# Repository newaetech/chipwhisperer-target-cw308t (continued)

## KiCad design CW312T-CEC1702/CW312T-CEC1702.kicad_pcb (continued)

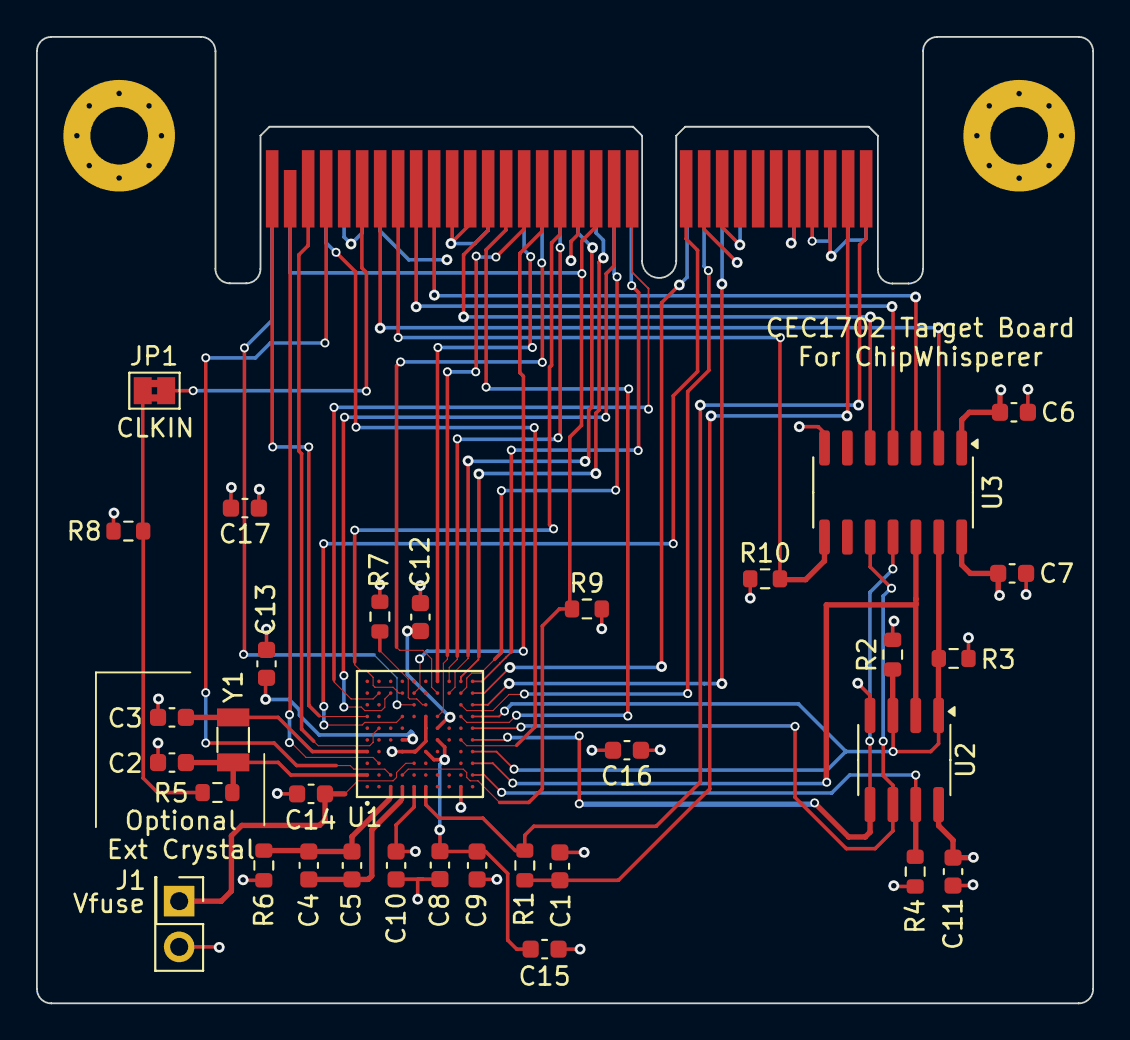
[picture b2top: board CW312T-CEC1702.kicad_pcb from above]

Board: 4 copper layers, 58.7 x 53.7 mm, 38 parts (0 on the bottom side), 47 nets.

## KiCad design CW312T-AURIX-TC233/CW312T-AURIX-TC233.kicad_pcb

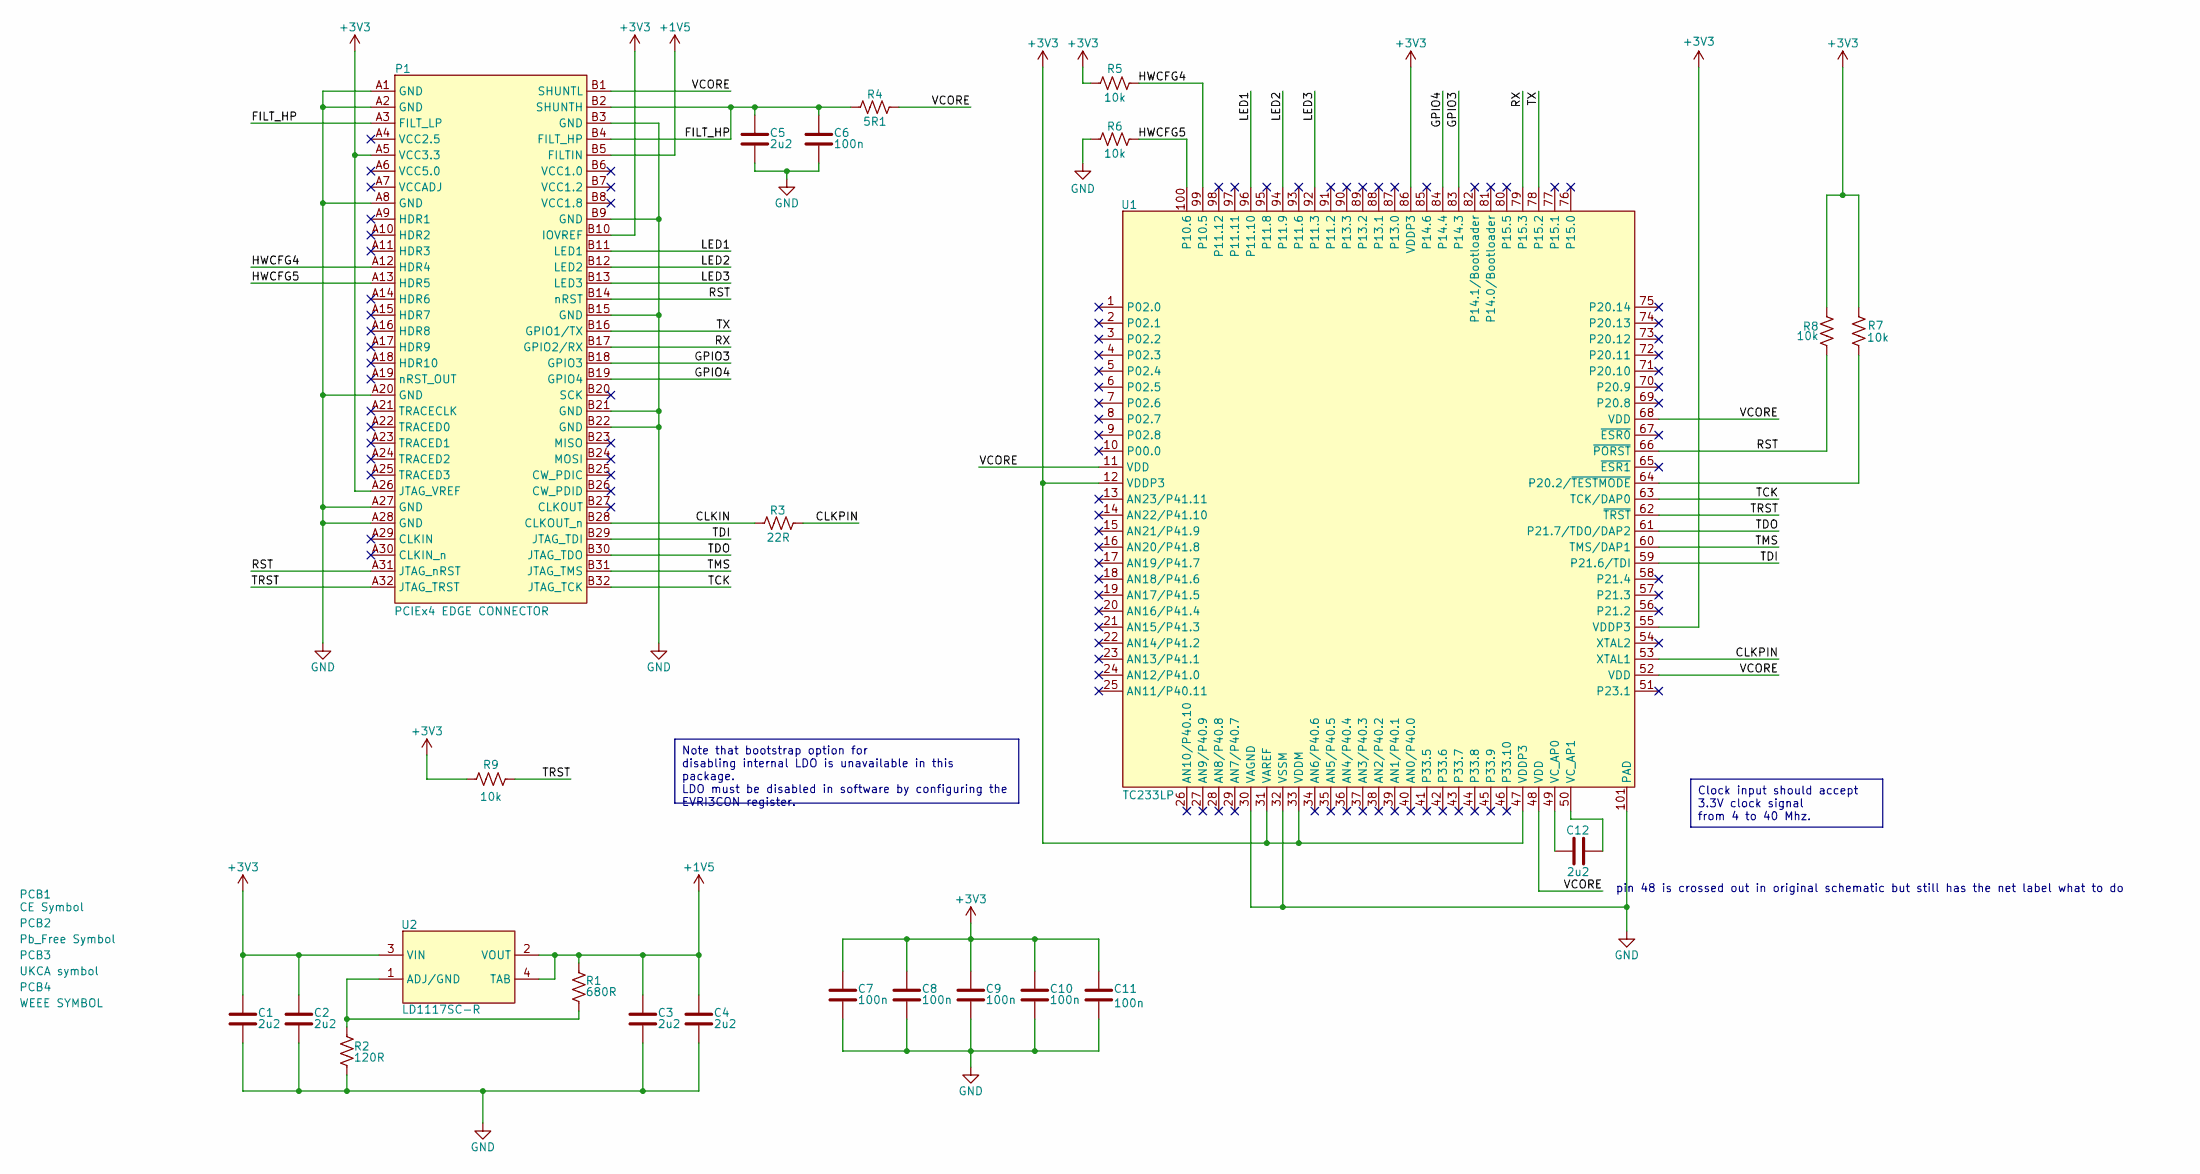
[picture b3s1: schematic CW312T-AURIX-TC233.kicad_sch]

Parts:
C1, C2, C3, C4, C5, C12: CAP_2u2_10V_0603; C_0603_1608Metric; Manufacturer Part Number CC0603KPX7R6BB225
C6, C7, C8, C9, C10, C11: CAP_100n_50V_0603; C_0603_1608Metric; Manufacturer Part Number CC0603KRX7R9BB104
P1: PCIEx4 EDGE CONNECTOR; CW312_Template
PCB1: CE Symbol; CE-Logo_8.5x6mm_SilkScreen
PCB2: Pb_Free Symbol; Pb_Free_8.0x8.0mm_SilkScreen
PCB3: UKCA symbol; UKCA-Logo_8x8mm_SilkScreen
PCB4: WEEE SYMBOL; WEEE-Logo_5.6x8mm_SilkScreen
R1: RES_680R_0603; R_0603_1608Metric; Manufacturer Part Number RC0603FR-07680RL
R2: RES_120R_0603; R_0603_1608Metric; Manufacturer Part Number RC0603FR-07120RL
R3: RES_22R_0603; R_0603_1608Metric; Manufacturer Part Number RC0603FR-0722RL
R4: RES_5R1_0603; R_0603_1608Metric; Manufacturer Part Number RC0603FR-075R1L
R5, R6, R7, R8, R9: RES_10k_0603; R_0603_1608Metric; Manufacturer Part Number RC0603FR-0710KL
U1: TC233LP32F200NACKXUMA1; TQFP-100-1EP_14x14mm_P0.5mm_EP5x5mm; Manufacturer Part Number TC233LP32F200NACKXUMA1
U2: LD1117SC-R; SOT-223; Manufacturer Part Number LD1117SC-R

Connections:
+1V5: C3.2, C4.2, P1.B5 (FILTIN), R1.2, U2.2 (VOUT), U2.4 (TAB)
+3V3: C1.2, C2.2, C7.2, C8.2, C9.2, C10.2, C11.2, P1.A5 (VCC3.3), P1.A26 (JTAG_VREF), P1.B10 (IOVREF), R5.1, R7.2, R8.2, R9.1, U1.12 (VDDP3), U1.31 (VAREF), U1.33 (VDDM), U1.47 (VDDP3), U1.55 (VDDP3), U1.86 (VDDP3), U2.3 (VIN)
/CLKIN: P1.B28 (CLKOUT_n), R3.2
/CLKPIN: R3.1, U1.53 (XTAL1)
/FILT_HP: C5.2, C6.2, P1.A3 (FILT_LP), P1.B2 (SHUNTH), P1.B4 (FILT_HP), R4.1
/GPIO3: P1.B18 (GPIO3), U1.83 (P14.3)
/GPIO4: P1.B19 (GPIO4), U1.84 (P14.4)
/HWCFG4: P1.A12 (HDR4), R5.2, U1.99 (P10.5)
/HWCFG5: P1.A13 (HDR5), R6.2, U1.100 (P10.6)
/LED1: P1.B11 (LED1), U1.96 (P11.10)
/LED2: P1.B12 (LED2), U1.94 (P11.9)
/LED3: P1.B13 (LED3), U1.92 (P11.3)
/RST: P1.A31 (JTAG_nRST), P1.B14 (nRST), R8.1, U1.66 (~PORST)
/RX: P1.B17 (GPIO2/RX), U1.79 (P15.3)
/TCK: P1.B32 (JTAG_TCK), U1.63 (TCK/DAP0)
/TDI: P1.B29 (JTAG_TDI), U1.59 (P21.6/TDI)
/TDO: P1.B30 (JTAG_TDO), U1.61 (P21.7/TDO/DAP2)
/TMS: P1.B31 (JTAG_TMS), U1.60 (TMS/DAP1)
/TRST: P1.A32 (JTAG_TRST), R9.2, U1.62 (~TRST)
/TX: P1.B16 (GPIO1/TX), U1.78 (P15.2)
/VCORE: P1.B1 (SHUNTL), R4.2, U1.11 (VDD), U1.48 (VDD), U1.52 (VDD), U1.68 (VDD)
GND: C1.1, C2.1, C3.1, C4.1, C5.1, C6.1, C7.1, C8.1, C9.1, C10.1, C11.1, P1.A1 (GND), P1.A2 (GND), P1.A8 (GND), P1.A20 (GND), P1.A27 (GND), P1.A28 (GND), P1.B3 (GND), P1.B9 (GND), P1.B15 (GND), P1.B21 (GND), P1.B22 (GND), R2.1, R6.1, U1.30 (VAGND), U1.32 (VSSM), U1.101 (PAD)
unnamed: R7.1, U1.64 (P20.2/~TESTMODE)
unnamed: C12.1, U1.49 (VC_AP0)
unnamed: C12.2, U1.50 (VC_AP1)
unnamed: R1.1, R2.2, U2.1 (ADJ/GND)

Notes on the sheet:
Clock input should accept 3.3V clock signal from 4 to 40 Mhz.
Note that bootstrap option for disabling internal LDO is unavailable in this package. LDO must be disabled in software by configuring the EVRI3CON register.
pin 48 is crossed out in original schematic but still has the net label what to do

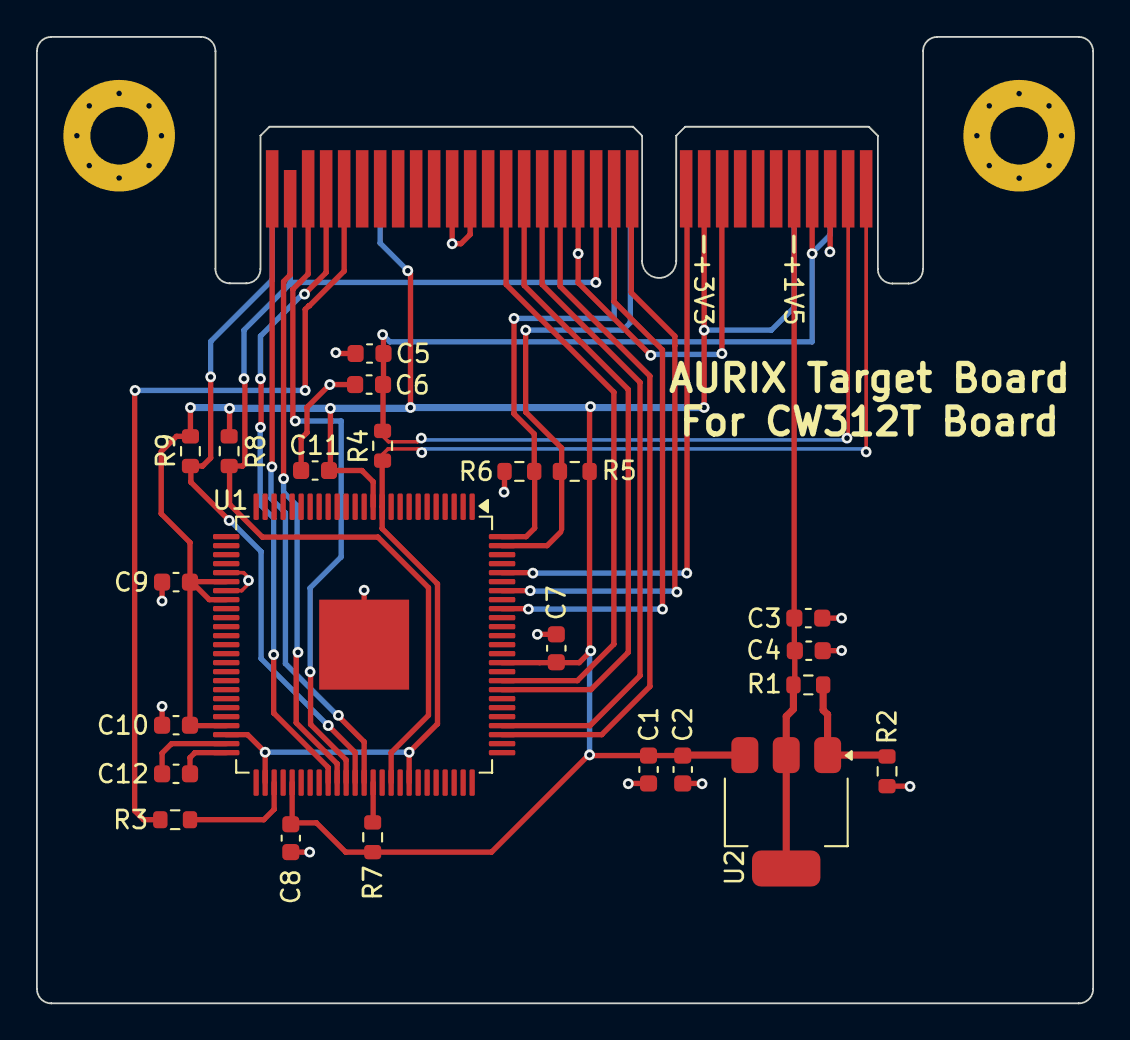
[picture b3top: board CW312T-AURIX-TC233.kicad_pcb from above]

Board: 2 copper layers, 58.7 x 53.7 mm, 28 parts (0 on the bottom side), 26 nets.

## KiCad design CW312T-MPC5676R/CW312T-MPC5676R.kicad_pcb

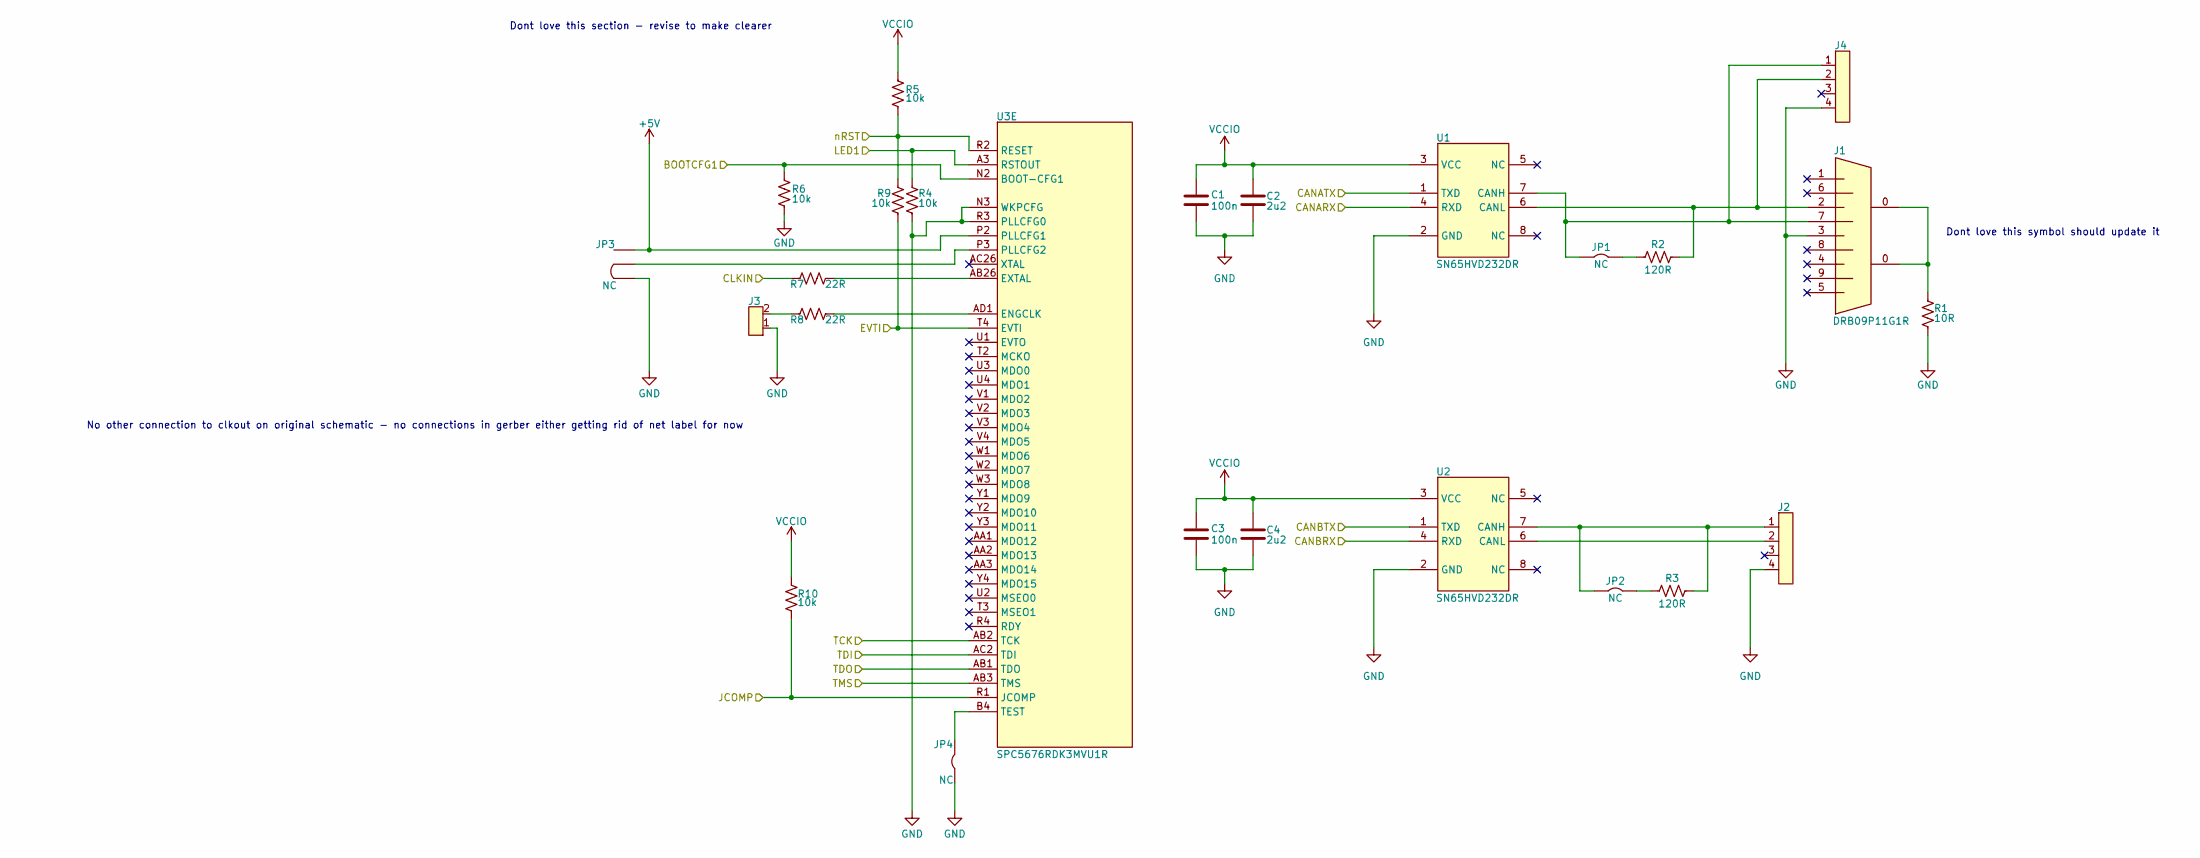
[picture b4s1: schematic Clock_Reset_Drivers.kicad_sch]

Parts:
C1, C3: CAP_100n_16V_0402; C_0402_1005Metric; Manufacturer Part Number CC0402KRX7R7BB104
C2, C4: CAP_2u2_10V_0603; C_0603_1608Metric; Manufacturer Part Number CC0603KPX7R6BB225
J1: DRB09P11G1R; DSUB-9_Male_Horizontal_P2.77x2.84mm_EdgePinOffset9.90mm_Hou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; Manufacturer Part Number 618009231421
J2, J4: HDR_4_2.54; PinHeader_1x04_P2.54mm_Vertical; Manufacturer Part Number HMTSW-104-23-L-S-237
J3: 2Pin_Header_2.54; PinHeader_2x01_P2.54mm_Vertical; Manufacturer Part Number M20-9990246
JP1, JP2, JP4: SolderJumper-2_P1.3mm_Bridged2Bar_Pad1.0x1.5mm
JP3: SolderJumper-3_P1.3mm_Bridged2Bar12_Pad1.0x1.5mm
R1: RES_10R_0603; R_0603_1608Metric; Manufacturer Part Number RC0603FR-0710RL
R2, R3: RES_120R_0603; R_0603_1608Metric; Manufacturer Part Number RC0603FR-07120RL
R4, R5, R6, R9, R10: RES_10k_0603; R_0603_1608Metric; Manufacturer Part Number RC0603FR-0710KL
R7, R8: RES_22R_0603; R_0603_1608Metric; Manufacturer Part Number RC0603FR-0722RL
U1, U2: SN65HVD232DR; SOIC-8_3.9x4.9mm_P1.27mm; Manufacturer Part Number SN65HVD232DR
U3: SPC5676RDK3MVU1R; BGA416C100P26X26_2700X2700X255N; Manufacturer Part Number SPC5676RDK3MVU1R

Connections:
+5V: JP3.3, U3.P2 (PLLCFG1); also elsewhere on the board
/CPU IO Bank 2/CANARX: U1.4 (RXD); also elsewhere on the board
/CPU IO Bank 2/CANATX: U1.1 (TXD); also elsewhere on the board
/CPU IO Bank 2/CANBRX: U2.4 (RXD); also elsewhere on the board
/CPU IO Bank 2/CANBTX: U2.1 (TXD); also elsewhere on the board
/CW312T-Connector/BOOTCFG1: R6.2, U3.N2 (BOOT-CFG1); also elsewhere on the board
/CW312T-Connector/CLKIN: R7.1; also elsewhere on the board
/CW312T-Connector/EVTI: R9.1, U3.T4 (EVTI); also elsewhere on the board
/CW312T-Connector/JCOMP: R10.1, U3.R1 (JCOMP); also elsewhere on the board
/CW312T-Connector/LED1: R4.2, U3.A3 (RSTOUT); also elsewhere on the board
/CW312T-Connector/TCK: U3.AB2 (TCK); also elsewhere on the board
/CW312T-Connector/TDI: U3.AC2 (TDI); also elsewhere on the board
/CW312T-Connector/TDO: U3.AB1 (TDO); also elsewhere on the board
/CW312T-Connector/TMS: U3.AB3 (TMS); also elsewhere on the board
/CW312T-Connector/nRST: R5.1, R9.2, U3.R2 (RESET); also elsewhere on the board
GND: C1.1, C2.1, C3.1, C4.1, J1.3, J2.4, J3.1, J4.4, JP3.1, JP4.2, R1.1, R4.1, R6.1, U1.2 (GND), U2.2 (GND), U3.N3 (WKPCFG), U3.R3 (PLLCFG0); also elsewhere on the board
unnamed: J1.0, R1.2
unnamed: J3.2, R8.1
unnamed: JP1.1, R2.1
unnamed: JP2.1, R3.1
unnamed: J1.7, J4.1, JP1.2, U1.7 (CANH)
unnamed: J1.2, J4.2, R2.2, U1.6 (CANL)
unnamed: J2.1, JP2.2, R3.2, U2.7 (CANH)
unnamed: J2.2, U2.6 (CANL)
unnamed: R8.2, U3.AD1 (ENGCLK)
unnamed: R7.2, U3.AB26 (EXTAL)
unnamed: JP3.2, U3.P3 (PLLCFG2)
unnamed: JP4.1, U3.B4 (TEST)
VCCIO: C1.2, C2.2, C3.2, C4.2, R5.2, R10.2, U1.3 (VCC), U2.3 (VCC); also elsewhere on the board

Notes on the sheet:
Dont love this symbol should update it
No other connection to clkout on original schematic - no connections in gerber either getting rid of net label for now
Dont love this section - revise to make clearer

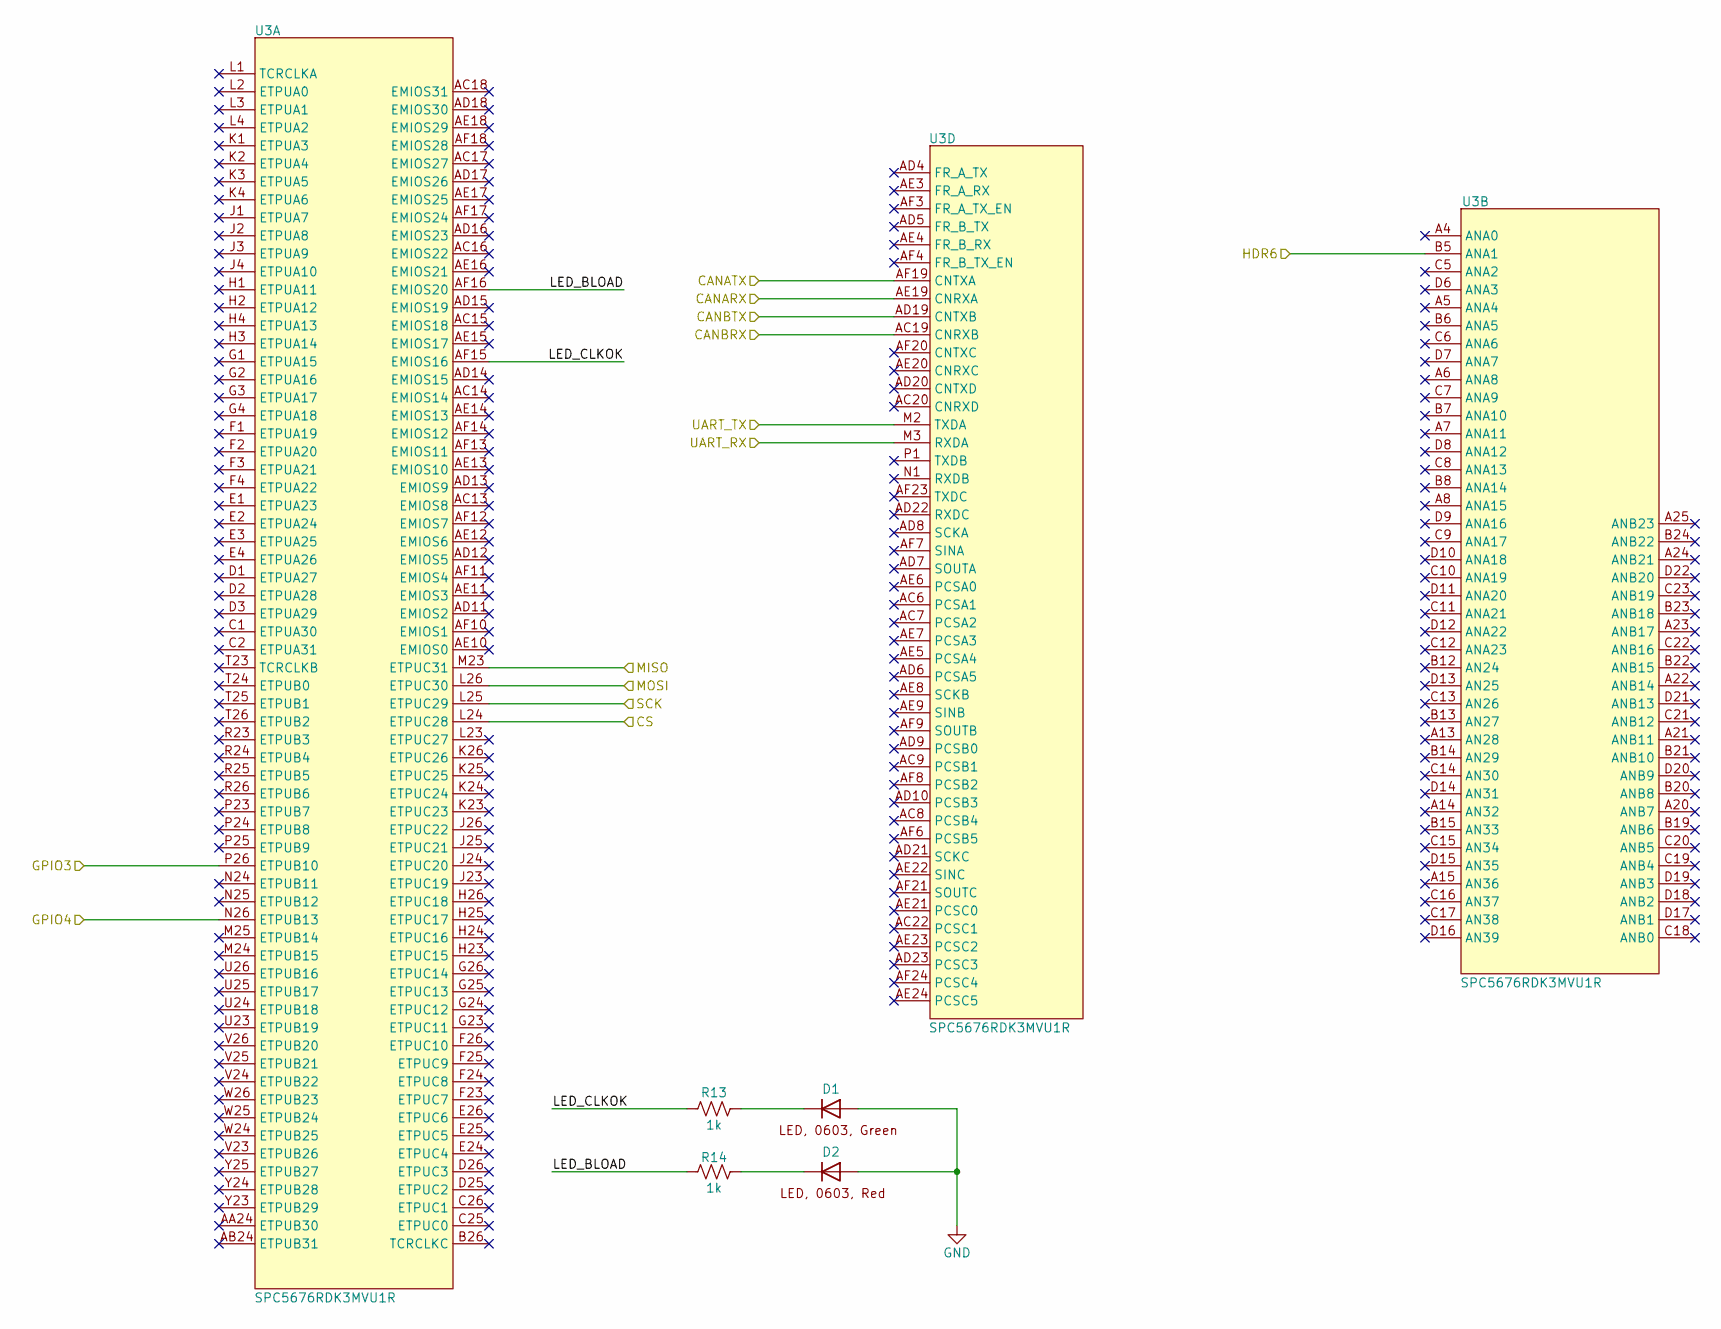
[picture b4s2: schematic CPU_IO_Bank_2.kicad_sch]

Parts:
D1, D2: APT1608SRCPRV; LED_0603_1608Metric; Manufacturer Part Number APT1608SRCPRV
R13, R14: RES_1k_0603; R_0603_1608Metric; Manufacturer Part Number RC0603FR-071KL
U3: SPC5676RDK3MVU1R; BGA416C100P26X26_2700X2700X255N; Manufacturer Part Number SPC5676RDK3MVU1R

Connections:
/CPU IO Bank 2/CANARX: U3.AE19 (CNRXA); also elsewhere on the board
/CPU IO Bank 2/CANATX: U3.AF19 (CNTXA); also elsewhere on the board
/CPU IO Bank 2/CANBRX: U3.AC19 (CNRXB); also elsewhere on the board
/CPU IO Bank 2/CANBTX: U3.AD19 (CNTXB); also elsewhere on the board
/CPU IO Bank 2/CS: U3.L24 (ETPUC28); also elsewhere on the board
/CPU IO Bank 2/GPIO3: U3.P26 (ETPUB10); also elsewhere on the board
/CPU IO Bank 2/GPIO4: U3.N26 (ETPUB13); also elsewhere on the board
/CPU IO Bank 2/HDR6: U3.B5 (ANA1); also elsewhere on the board
/CPU IO Bank 2/LED_BLOAD: R14.1, U3.AF16 (EMIOS20)
/CPU IO Bank 2/LED_CLKOK: R13.1, U3.AF15 (EMIOS16)
/CPU IO Bank 2/MISO: U3.M23 (ETPUC31); also elsewhere on the board
/CPU IO Bank 2/MOSI: U3.L26 (ETPUC30); also elsewhere on the board
/CPU IO Bank 2/SCK: U3.L25 (ETPUC29); also elsewhere on the board
/CPU IO Bank 2/UART_RX: U3.M3 (RXDA); also elsewhere on the board
/CPU IO Bank 2/UART_TX: U3.M2 (TXDA); also elsewhere on the board
GND: D1.2, D2.2; also elsewhere on the board
unnamed: D1.1, R13.2
unnamed: D2.1, R14.2

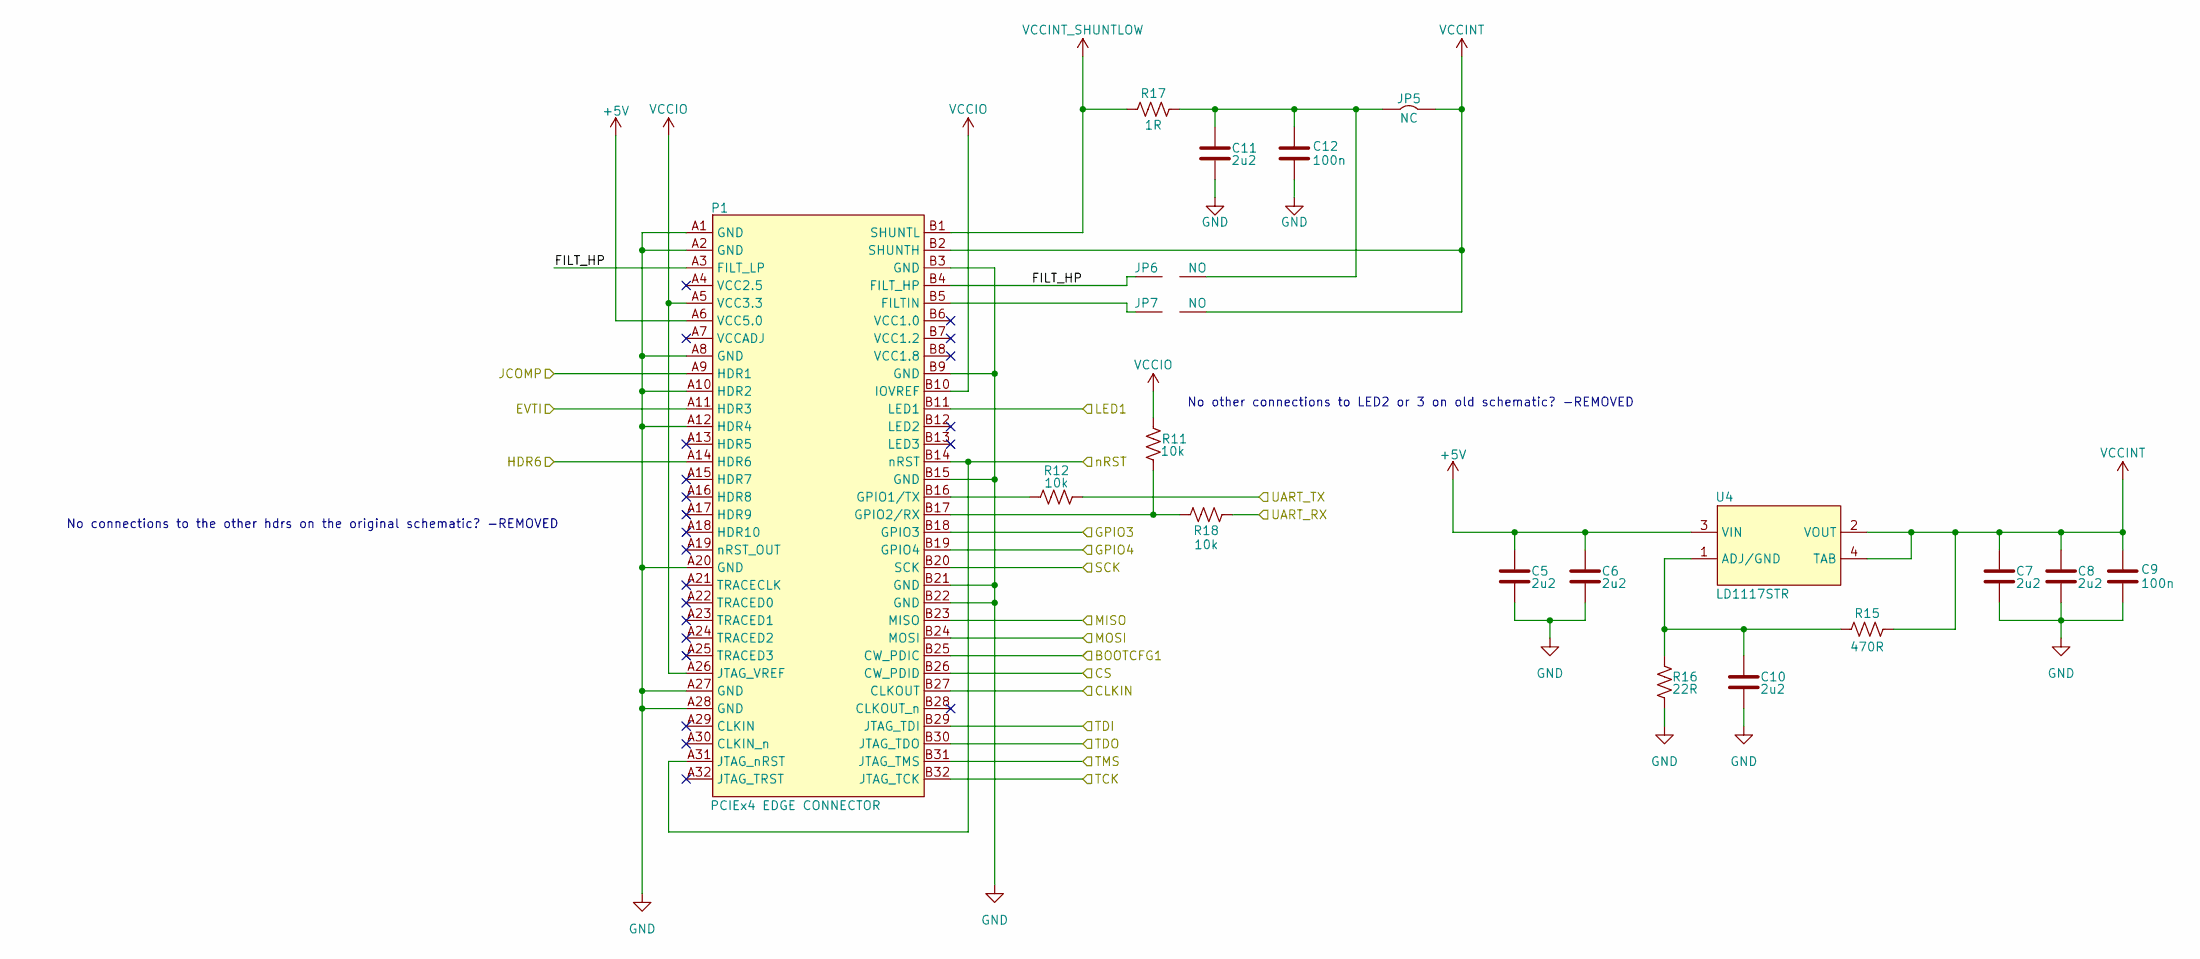
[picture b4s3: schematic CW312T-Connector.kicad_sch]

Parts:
C5, C6, C7, C8, C10, C11: CAP_2u2_10V_0603; C_0603_1608Metric; Manufacturer Part Number CC0603KPX7R6BB225
C9, C12: CAP_100n_16V_0402; C_0402_1005Metric; Manufacturer Part Number CC0402KRX7R7BB104
JP5: SolderJumper-2_P1.3mm_Bridged2Bar_Pad1.0x1.5mm
JP6, JP7: SolderJumper-2_P1.3mm_Open_Pad1.0x1.5mm
P1: PCIEx4 EDGE CONNECTOR; CW312_Template
R11, R12, R18: RES_10k_0603; R_0603_1608Metric; Manufacturer Part Number RC0603FR-0710KL
R15: RES_470R_0603; R_0603_1608Metric; Manufacturer Part Number RC0603FR-13470RL
R16: RES_22R_0603; R_0603_1608Metric; Manufacturer Part Number RC0603FR-0722RL
R17: RES_1R_0805; R_0805_2012Metric; Manufacturer Part Number RC0805FR-071RL
U4: LD1117STR; SOT-223; Manufacturer Part Number LD1117STR

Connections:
+5V: C5.2, C6.2, P1.A6 (VCC5.0), U4.3 (VIN); also elsewhere on the board
/CPU IO Bank 2/CS: P1.B26 (CW_PDID); also elsewhere on the board
/CPU IO Bank 2/GPIO3: P1.B19 (GPIO4); also elsewhere on the board
/CPU IO Bank 2/GPIO4: P1.B18 (GPIO3); also elsewhere on the board
/CPU IO Bank 2/HDR6: P1.A14 (HDR6); also elsewhere on the board
/CPU IO Bank 2/MISO: P1.B23 (MISO); also elsewhere on the board
/CPU IO Bank 2/MOSI: P1.B24 (MOSI); also elsewhere on the board
/CPU IO Bank 2/SCK: P1.B20 (SCK); also elsewhere on the board
/CPU IO Bank 2/UART_RX: R18.2; also elsewhere on the board
/CPU IO Bank 2/UART_TX: R12.2; also elsewhere on the board
/CW312T-Connector/BOOTCFG1: P1.B25 (CW_PDIC); also elsewhere on the board
/CW312T-Connector/CLKIN: P1.B27 (CLKOUT); also elsewhere on the board
/CW312T-Connector/EVTI: P1.A11 (HDR3); also elsewhere on the board
/CW312T-Connector/FILT_HP: JP6.2, P1.A3 (FILT_LP), P1.B4 (FILT_HP)
/CW312T-Connector/JCOMP: P1.A9 (HDR1); also elsewhere on the board
/CW312T-Connector/LED1: P1.B11 (LED1); also elsewhere on the board
/CW312T-Connector/TCK: P1.B32 (JTAG_TCK); also elsewhere on the board
/CW312T-Connector/TDI: P1.B29 (JTAG_TDI); also elsewhere on the board
/CW312T-Connector/TDO: P1.B30 (JTAG_TDO); also elsewhere on the board
/CW312T-Connector/TMS: P1.B31 (JTAG_TMS); also elsewhere on the board
/CW312T-Connector/nRST: P1.A31 (JTAG_nRST), P1.B14 (nRST); also elsewhere on the board
GND: C5.1, C6.1, C7.1, C8.1, C9.1, C10.1, C11.1, C12.1, P1.A1 (GND), P1.A2 (GND), P1.A8 (GND), P1.A10 (HDR2), P1.A12 (HDR4), P1.A20 (GND), P1.A27 (GND), P1.A28 (GND), P1.B3 (GND), P1.B9 (GND), P1.B15 (GND), P1.B21 (GND), P1.B22 (GND), R16.1; also elsewhere on the board
unnamed: C11.2, C12.2, JP5.2, JP6.1, R17.2
unnamed: JP7.2, P1.B5 (FILTIN)
unnamed: P1.B16 (GPIO1/TX), R12.1
unnamed: P1.B17 (GPIO2/RX), R11.1, R18.1
unnamed: C10.2, R15.1, R16.2, U4.1 (ADJ/GND)
VCCINT: C7.2, C8.2, C9.2, JP5.1, JP7.1, P1.B2 (SHUNTH), R15.2, U4.2 (VOUT), U4.4 (TAB)
VCCINT_SHUNTLOW: P1.B1 (SHUNTL), R17.1; also elsewhere on the board
VCCIO: P1.A5 (VCC3.3), P1.A26 (JTAG_VREF), P1.B10 (IOVREF), R11.2; also elsewhere on the board

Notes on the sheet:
No connections to the other hdrs on the original schematic? -REMOVED
No other connections to LED2 or 3 on old schematic? -REMOVED

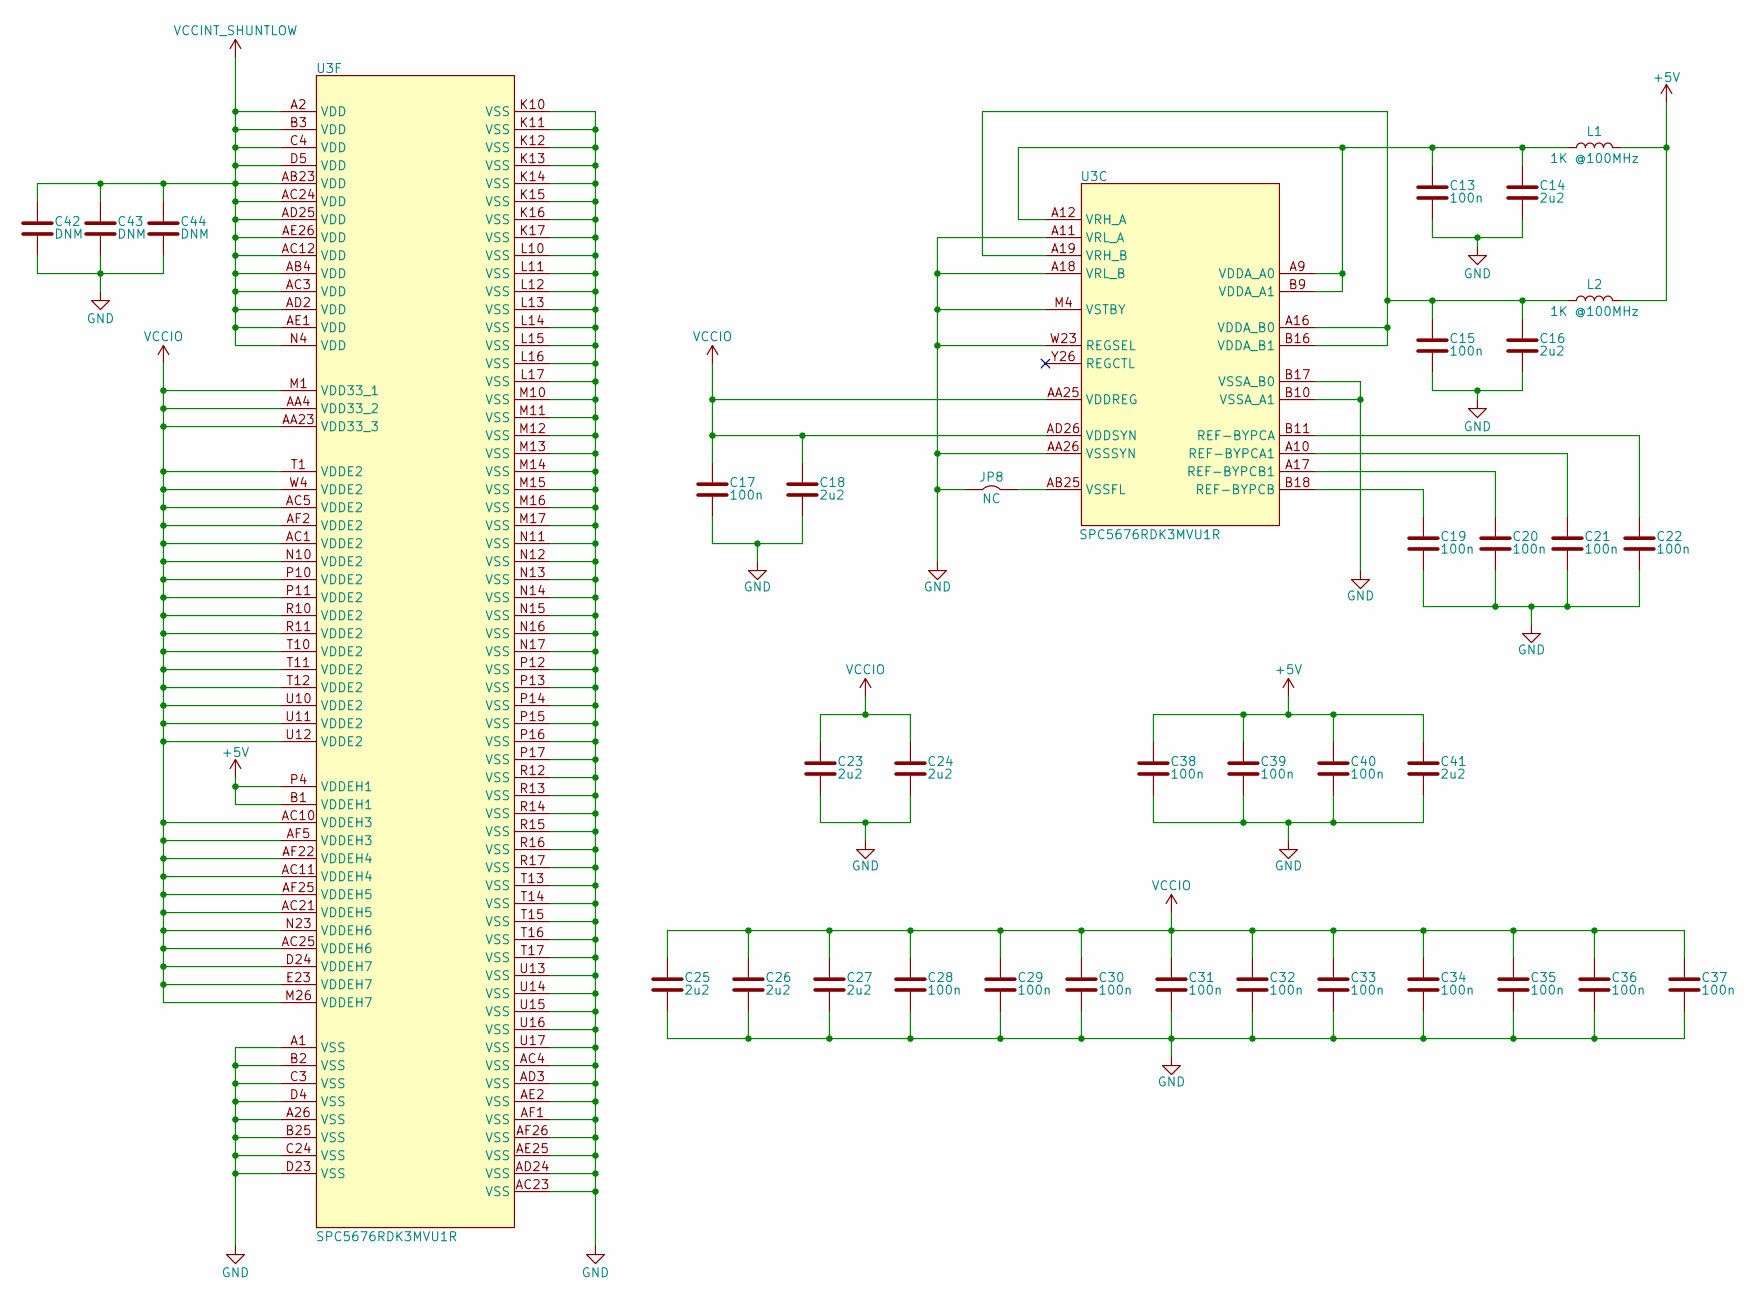
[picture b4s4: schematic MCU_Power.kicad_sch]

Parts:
C13, C15, C17, C19, C20, C21, C22, C28, C29, C30, C31, C32, C33, C34, C35, C36, C37, C38, C39, C40: CAP_100n_16V_0402; C_0402_1005Metric; Manufacturer Part Number CC0402KRX7R7BB104
C14, C16, C18, C23, C24, C25, C26, C27, C41: CAP_2u2_10V_0603; C_0603_1608Metric; Manufacturer Part Number CC0603KPX7R6BB225
C42, C43, C44: CAP_DNM_0402; C_0402_1005Metric
JP8: SolderJumper-2_P1.3mm_Bridged2Bar_Pad1.0x1.5mm
L1, L2: IND_1K_0603; L_0603_1608Metric; Manufacturer Part Number FBMH1608HM102-T
U3: SPC5676RDK3MVU1R; BGA416C100P26X26_2700X2700X255N; Manufacturer Part Number SPC5676RDK3MVU1R

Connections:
+5V: C38.2, C39.2, C40.2, C41.2, L1.2, L2.2, U3.B1 (VDDEH1), U3.P4 (VDDEH1); also elsewhere on the board
GND: C13.1, C14.1, C15.1, C16.1, C17.1, C18.1, C19.1, C20.1, C21.1, C22.1, C23.1, C24.1, C25.1, C26.1, C27.1, C28.1, C29.1, C30.1, C31.1, C32.1, C33.1, C34.1, C35.1, C36.1, C37.1, C38.1, C39.1, C40.1, C41.1, C42.1, C43.1, C44.1, JP8.2, U3.A1 (VSS), U3.A11 (VRL_A), U3.A18 (VRL_B), U3.A26 (VSS), U3.AA26 (VSSSYN), U3.AC4 (VSS), U3.AC23 (VSS), U3.AD3 (VSS), U3.AD24 (VSS), U3.AE2 (VSS), U3.AE25 (VSS), U3.AF1 (VSS), U3.AF26 (VSS), U3.B2 (VSS), U3.B10 (VSSA_A1), U3.B17 (VSSA_B0), U3.B25 (VSS), U3.C3 (VSS), U3.C24 (VSS), U3.D4 (VSS), U3.D23 (VSS), U3.K10 (VSS), U3.K11 (VSS), U3.K12 (VSS), U3.K13 (VSS), U3.K14 (VSS), U3.K15 (VSS), U3.K16 (VSS), U3.K17 (VSS), U3.L10 (VSS), U3.L11 (VSS), U3.L12 (VSS), U3.L13 (VSS), U3.L14 (VSS), U3.L15 (VSS), U3.L16 (VSS), U3.L17 (VSS), U3.M4 (VSTBY), U3.M10 (VSS), U3.M11 (VSS), U3.M12 (VSS), U3.M13 (VSS), U3.M14 (VSS), U3.M15 (VSS), U3.M16 (VSS), U3.M17 (VSS), U3.N11 (VSS), U3.N12 (VSS), U3.N13 (VSS), U3.N14 (VSS), U3.N15 (VSS), U3.N16 (VSS), U3.N17 (VSS), U3.P12 (VSS), U3.P13 (VSS), U3.P14 (VSS), U3.P15 (VSS), U3.P16 (VSS), U3.P17 (VSS), U3.R12 (VSS), U3.R13 (VSS), U3.R14 (VSS), U3.R15 (VSS), U3.R16 (VSS), U3.R17 (VSS), U3.T13 (VSS), U3.T14 (VSS), U3.T15 (VSS), U3.T16 (VSS), U3.T17 (VSS), U3.U13 (VSS), U3.U14 (VSS), U3.U15 (VSS), U3.U16 (VSS), U3.U17 (VSS), U3.W23 (REGSEL); also elsewhere on the board
unnamed: C21.2, U3.A10 (REF-BYPCA1)
unnamed: C22.2, U3.B11 (REF-BYPCA)
unnamed: C20.2, U3.A17 (REF-BYPCB1)
unnamed: C19.2, U3.B18 (REF-BYPCB)
unnamed: C13.2, C14.2, L1.1, U3.A9 (VDDA_A0), U3.A12 (VRH_A), U3.B9 (VDDA_A1)
unnamed: C15.2, C16.2, L2.1, U3.A16 (VDDA_B0), U3.A19 (VRH_B), U3.B16 (VDDA_B1)
unnamed: JP8.1, U3.AB25 (VSSFL)
VCCINT_SHUNTLOW: C42.2, C43.2, C44.2, U3.A2 (VDD), U3.AB4 (VDD), U3.AB23 (VDD), U3.AC3 (VDD), U3.AC12 (VDD), U3.AC24 (VDD), U3.AD2 (VDD), U3.AD25 (VDD), U3.AE1 (VDD), U3.AE26 (VDD), U3.B3 (VDD), U3.C4 (VDD), U3.D5 (VDD), U3.N4 (VDD); also elsewhere on the board
VCCIO: C17.2, C18.2, C23.2, C24.2, C25.2, C26.2, C27.2, C28.2, C29.2, C30.2, C31.2, C32.2, C33.2, C34.2, C35.2, C36.2, C37.2, U3.AA4 (VDD33_2), U3.AA23 (VDD33_3), U3.AA25 (VDDREG), U3.AC1 (VDDE2), U3.AC5 (VDDE2), U3.AC10 (VDDEH3), U3.AC11 (VDDEH4), U3.AC21 (VDDEH5), U3.AC25 (VDDEH6), U3.AD26 (VDDSYN), U3.AF2 (VDDE2), U3.AF5 (VDDEH3), U3.AF22 (VDDEH4), U3.AF25 (VDDEH5), U3.D24 (VDDEH7), U3.E23 (VDDEH7), U3.M1 (VDD33_1), U3.M26 (VDDEH7), U3.N10 (VDDE2), U3.N23 (VDDEH6), U3.P10 (VDDE2), U3.P11 (VDDE2), U3.R10 (VDDE2), U3.R11 (VDDE2), U3.T1 (VDDE2), U3.T10 (VDDE2), U3.T11 (VDDE2), U3.T12 (VDDE2), U3.U10 (VDDE2), U3.U11 (VDDE2), U3.U12 (VDDE2), U3.W4 (VDDE2); also elsewhere on the board

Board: 2 copper layers, 83 parts (0 on the bottom side), 57 nets, no tracks yet.
